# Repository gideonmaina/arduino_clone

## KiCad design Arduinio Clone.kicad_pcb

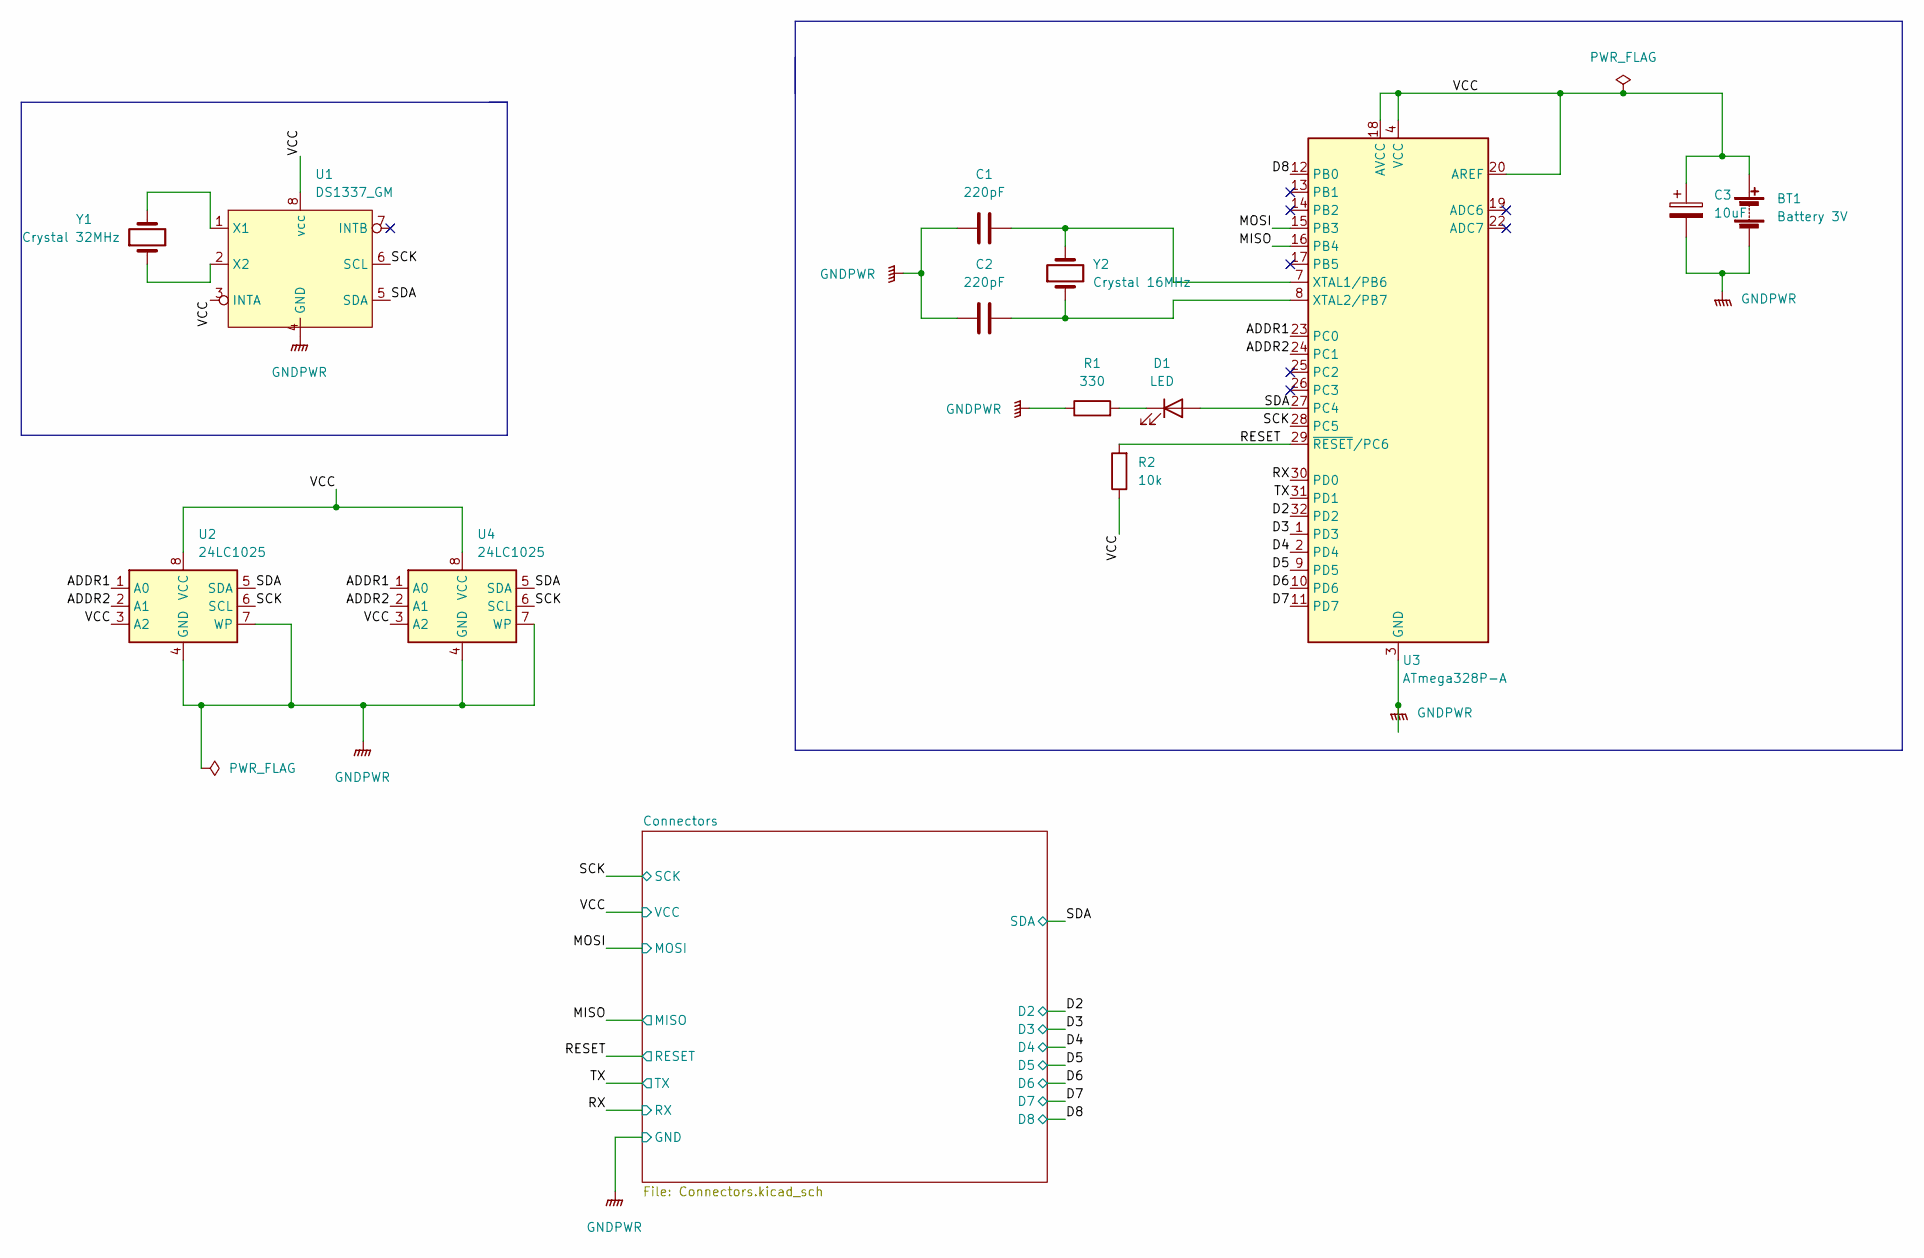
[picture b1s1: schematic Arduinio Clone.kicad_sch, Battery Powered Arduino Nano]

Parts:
BT1: Battery 3V; PinHeader_1x02_P2.54mm_Vertical
C1, C2: 220pF; C_0805_2012Metric
C3: 10uF; C_0805_2012Metric
D1: LED; LED_0805_2012Metric
R1: 330; R_0805_2012Metric_Pad1.20x1.40mm_HandSolder
R2: 10k; R_0805_2012Metric_Pad1.20x1.40mm_HandSolder
U1: DS1337_GM; SO-8_5.3x6.2mm_P1.27mm
U2, U4: 24LC1025; SOIC-8_3.9x4.9mm_P1.27mm
U3: ATmega328P-A; TQFP-32_7x7mm_P0.8mm
Y1: Crystal 32MHz; Crystal_SMD_MicroCrystal_CC7V-T1A-2Pin_3.2x1.5mm
Y2: Crystal 16MHz; Crystal_SMD_5032-2Pin_5.0x3.2mm_HandSoldering

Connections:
/ADDR1: U2.1 (A0), U3.23 (PC0), U4.1 (A0)
/ADDR2: U2.2 (A1), U3.24 (PC1), U4.2 (A1)
/D2: U3.32 (PD2); also elsewhere on the board
/D3: U3.1 (PD3); also elsewhere on the board
/D4: U3.2 (PD4); also elsewhere on the board
/D5: U3.9 (PD5); also elsewhere on the board
/D6: U3.10 (PD6); also elsewhere on the board
/D7: U3.11 (PD7); also elsewhere on the board
/D8: U3.12 (PB0); also elsewhere on the board
/MISO: U3.16 (PB4); also elsewhere on the board
/MOSI: U3.15 (PB3); also elsewhere on the board
/RESET: R2.2, U3.29 (~RESET/PC6); also elsewhere on the board
/RX: U3.30 (PD0); also elsewhere on the board
/SCK: U1.6 (SCL), U2.6 (SCL), U3.28 (PC5), U4.6 (SCL); also elsewhere on the board
/SDA: D1.2 (A), U1.5 (SDA), U2.5 (SDA), U3.27 (PC4), U4.5 (SDA); also elsewhere on the board
/TX: U3.31 (PD1); also elsewhere on the board
/VCC: BT1.1 (+), C3.1, R2.1, U1.3 (INTA), U1.8 (vcc), U2.3 (A2), U2.8 (VCC), U3.4 (VCC), U3.6 (VCC), U3.18 (AVCC), U3.20 (AREF), U4.3 (A2), U4.8 (VCC); also elsewhere on the board
GNDPWR: BT1.2 (-), C1.1, C2.1, C3.2, R1.1, U1.4 (GND), U2.4 (GND), U2.7 (WP), U3.3 (GND), U3.5 (GND), U3.21 (GND), U4.4 (GND), U4.7 (WP); also elsewhere on the board
unnamed: C1.2, U3.7 (XTAL1/PB6), Y2.2
unnamed: C2.2, U3.8 (XTAL2/PB7), Y2.1
unnamed: D1.1 (K), R1.2
unnamed: U1.1 (X1), Y1.2
unnamed: U1.2 (X2), Y1.1

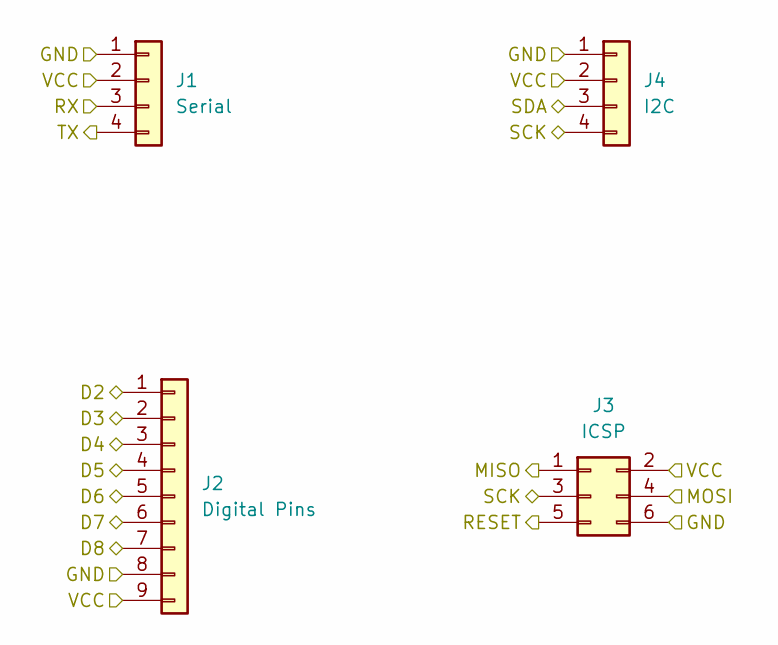
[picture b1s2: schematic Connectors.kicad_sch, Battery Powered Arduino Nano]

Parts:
J1: Serial; PinHeader_1x04_P2.54mm_Vertical
J2: Digital Pins; PinHeader_1x09_P2.54mm_Vertical
J3: ICSP; PinHeader_2x03_P2.54mm_Vertical
J4: I2C; PinHeader_1x04_P2.54mm_Vertical

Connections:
/D2: J2.1; also elsewhere on the board
/D3: J2.2; also elsewhere on the board
/D4: J2.3; also elsewhere on the board
/D5: J2.4; also elsewhere on the board
/D6: J2.5; also elsewhere on the board
/D7: J2.6; also elsewhere on the board
/D8: J2.7; also elsewhere on the board
/MISO: J3.1; also elsewhere on the board
/MOSI: J3.4; also elsewhere on the board
/RESET: J3.5; also elsewhere on the board
/RX: J1.3; also elsewhere on the board
/SCK: J3.3, J4.4; also elsewhere on the board
/SDA: J4.3; also elsewhere on the board
/TX: J1.4; also elsewhere on the board
/VCC: J1.2, J2.9, J3.2, J4.2; also elsewhere on the board
GNDPWR: J1.1, J2.8, J3.6, J4.1; also elsewhere on the board

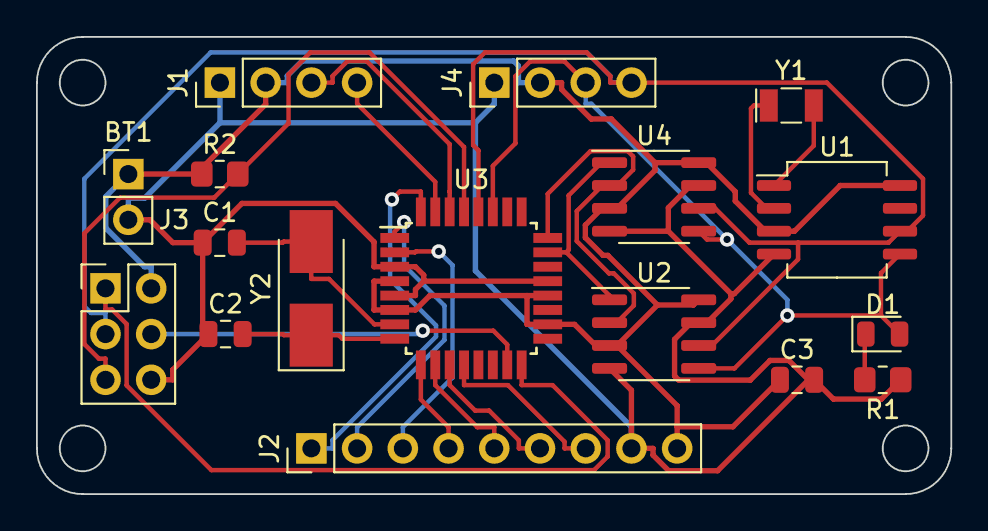
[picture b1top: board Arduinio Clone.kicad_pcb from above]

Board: 2 copper layers, 50.8 x 25.4 mm, 17 parts (0 on the bottom side), 23 nets.

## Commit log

2022-04-27 Setup Title Block to Schematic Sheet
2022-04-27 Added child connectors schematic and symbols
2022-04-28 Added README file
2022-05-04 Added Atmega328p-A symbol
2022-05-05 Added custom DS1337 RTC symbol
2022-05-05 Added crystals to schematic
2022-05-09 Annotation
2022-05-09 Component associations and values
2022-05-10 Added .gitignore file to untrack local backups
2022-05-10 Connectors sheet wiring
2022-05-10 Root sheet wiring
2022-05-11 ERC run
2022-05-11 Started working on PCB new
2022-05-11 Added design rules
2022-05-12 Component placement in PCB
2022-05-12 Made edge cuts
2022-05-12 Exported 2 layer DSN
2022-05-16 Done routing with Freefrouter and exported session file
2022-05-16 Imported generated Spectra sessionfile and ran DRC
2022-05-18 generated 2 layer board
2022-05-18 Exported 4 layer Spectra dsn
2022-05-18 Generated 4 layer Spectra session file
2022-05-18 Saved fully routed 4 layer board
2022-05-18 Added Back silkscreen text
